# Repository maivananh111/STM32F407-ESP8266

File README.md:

# STM32F407-ESP8266

STM32F407VGT6 and ESP8266 board

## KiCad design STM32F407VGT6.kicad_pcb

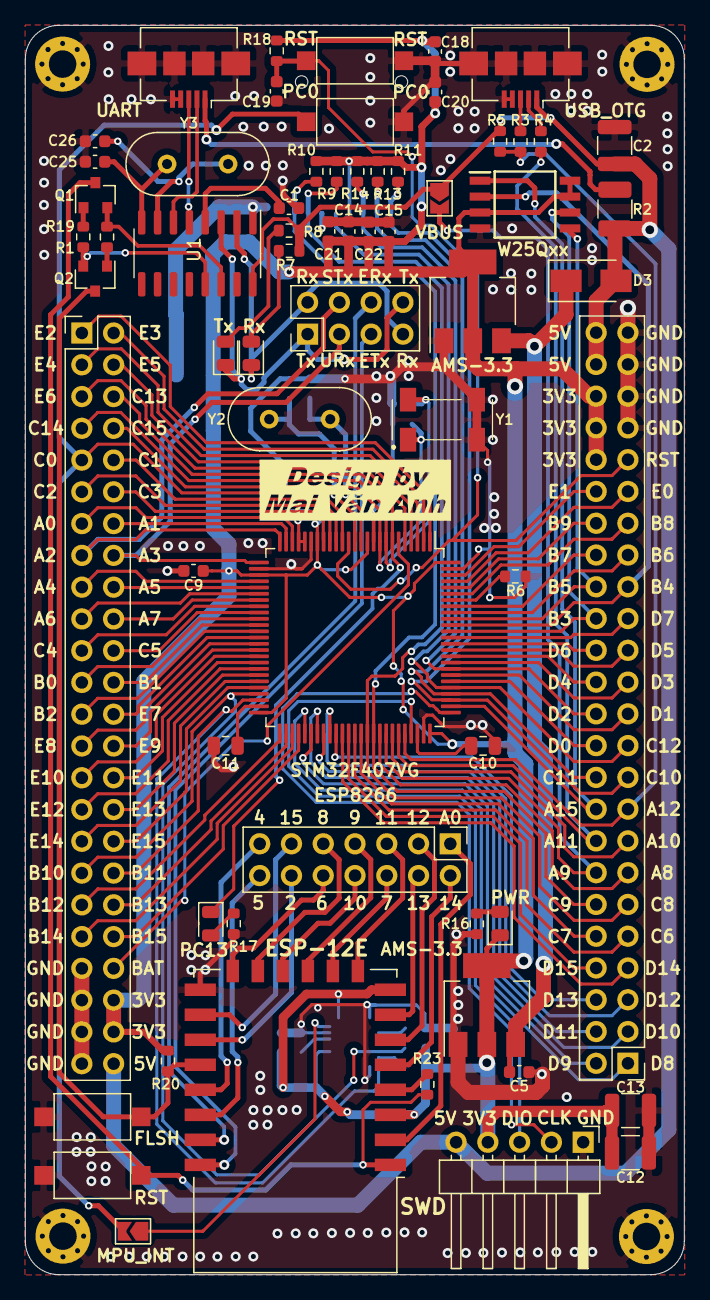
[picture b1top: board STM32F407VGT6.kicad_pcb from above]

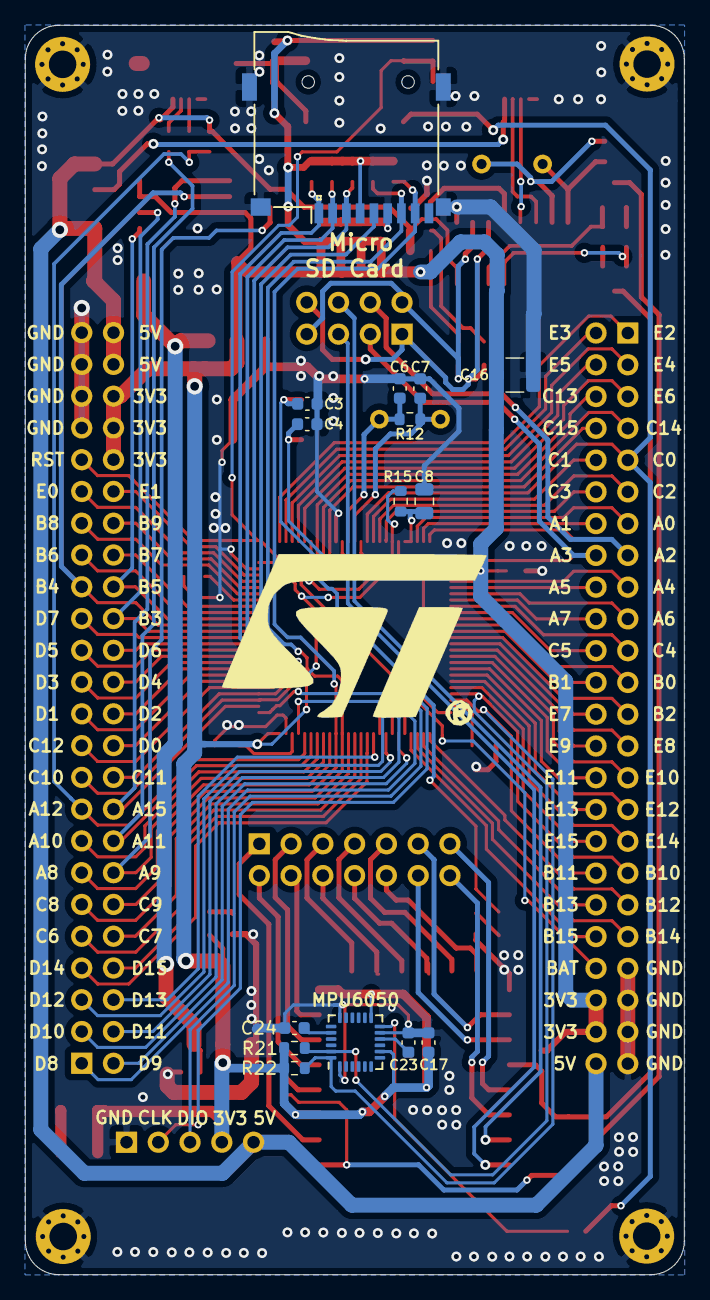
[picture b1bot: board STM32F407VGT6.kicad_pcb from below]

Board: 2 copper layers, 52.7 x 99.9 mm, 85 parts (15 on the bottom side), 132 nets.

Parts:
 : Design
 #2: 1; MountingHole_2.2mm_M2_Pad_Via
 #3: 2; MountingHole_2.2mm_M2_Pad_Via
 #4: 3; MountingHole_2.2mm_M2_Pad_Via
 #5: 4; MountingHole_2.2mm_M2_Pad_Via
 #6: UART_SELECT; PinHeader_2x04_P2.54mm_Vertical
 #7: A; PinHeader_2x24_P2.54mm_Vertical
 #8: B; PinHeader_2x24_P2.54mm_Vertical
AMS-3.3, AMS-3.3#2: AMS1117-3.3; SOT-223-3_TabPin2
C1, C5, C9, C14, C15, C17, C18, C19, C20, C21, C22, C23: 100nF; C_0603_1608Metric
C2, C12, C13, C16: 100uF; C_1210_3225Metric
C3, C4, C6, C7, C25, C26: 22pF; C_0603_1608Metric
C8, C10, C11: 1uF; C_0805_2012Metric
C24: 2.2nF; C_0603_1608Metric
D3: US2AA; D_SMA
ESP8266: ESP_IO; PinHeader_2x07_P2.54mm_Vertical
ESP-12E: ESP-12E
FLSH: ESP_FLS; SW_SPST_CK_RS282G05A3
MPU6050: MPU-6050; InvenSense_QFN-24_4x4mm_P0.5mm
MPU_INT: MPU_INT; SolderJumper-2_P1.3mm_Open_TrianglePad1.0x1.5mm
PC0: USE_BTN; SW_SPST_CK_RS282G05A3
PC13: LED; LED_0805_2012Metric
PWR: LED; LED_0805_2012Metric
Q1, Q2: BC847; SOT-23
R1, R3, R4, R5, R9, R10, R11, R13, R14, R18, R19: 15K; R_0603_1608Metric
R2: 0.1; R_1210_3225Metric_Pad1.30x2.65mm_HandSolder
R6, R20: 10K; R_0603_1608Metric
R7, R8: 1K; R_0603_1608Metric
R12: 100M; R_0603_1608Metric
R15: 47; R_0603_1608Metric
R16, R17: 220; R_0603_1608Metric
R21, R22: 4K7; R_0603_1608Metric
R23: 470; R_0603_1608Metric
RST: ESP_RST; SW_SPST_CK_RS282G05A3
RST#2: RESET; SW_SPST_CK_RS282G05A3
Rx: LED; LED_0805_2012Metric
STM32F407VG: STM32F407VGTx; LQFP-100_14x14mm_P0.5mm
SWD: SWD Programmer; PinHeader_1x05_P2.54mm_Horizontal
Tx: LED; LED_0805_2012Metric
U1: CH340G; SOIC-16_3.9x9.9mm_P1.27mm
UART: USB_B_Micro; USB_Micro-B_Amphenol_10104110_Horizontal
USB_OTG: USB_B_Micro; USB_Micro-B_Amphenol_10104110_Horizontal
VBUS: VBUS; SolderJumper-2_P1.3mm_Open_TrianglePad1.0x1.5mm
W25Qxx: W25Q128JWSIQ; SOIC127P790X216-8N
XS1: SD_Card; Conn_uSDcard
Y1: 32.768KHz; MC306327680KE3ROHS
Y2: 25MHz; Crystal_HC49-4H_Vertical
Y3: 12MHz; Crystal_HC49-4H_Vertical

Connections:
+3V3: #7.44, #7.46, #8.40, #8.42, #8.44, AMS-3.3.2, AMS-3.3#2.2, C9.1, C12.1, C13.1, C14.1, C15.1, C16.1, C17.1, C18.1, C20.1, C21.1, C22.1, ESP-12E.3, ESP-12E.8, MPU6050.8, MPU6050.13, PWR.1, R9.2, R10.2, R11.2, R13.2, R14.2, R15.1, R18.2, R20.2, R21.1, R22.1, STM32F407VG.11, STM32F407VG.19, STM32F407VG.28, STM32F407VG.50, STM32F407VG.75, STM32F407VG.100, SWD.4, W25Qxx.3, W25Qxx.7, W25Qxx.8, XS1.4
+5V: #7.48, #8.46, #8.48, C2.1, D3.2, R2.1, R5.2, R7.2, R8.2, SWD.5, U1.16, USB_OTG.1, VBUS.1
ADC: ESP8266.1, ESP-12E.2
CHE1: C25.2, U1.8, Y3.2
CHE2: C26.2, U1.7, Y3.1
ESP_RST: ESP-12E.1, Q1.3, R23.2, RST.2
ESP_Rx: #6.6, ESP-12E.21
ESP_Tx: #6.5, ESP-12E.22
GND: #2.1, #3.1, #4.1, #5.1, #7.41, #7.43, #7.45, #7.47, #8.41, #8.43, #8.45, #8.47, AMS-3.3.1, AMS-3.3#2.1, C1.2, C2.2, C3.1, C4.1, C5.2, C6.1, C7.1, C8.2, C9.2, C10.1, C11.1, C12.2, C13.2, C14.2, C15.2, C16.2, C17.2, C18.2, C19.2, C20.2, C21.2, C22.2, C23.1, C24.1, C25.1, C26.1, ESP-12E.15, FLSH.1, MPU6050.1, MPU6050.11, MPU6050.18, PC0.1, R6.1, R16.2, R17.2, RST.1, RST#2.1, STM32F407VG.10, STM32F407VG.20, STM32F407VG.27, STM32F407VG.74, STM32F407VG.99, SWD.1, U1.1, UART.4, UART.5, UART.6, USB_OTG.4, USB_OTG.5, USB_OTG.6, W25Qxx.4, XS1.6, Y1.2, Y1.3
GPIO0: ESP-12E.18, FLSH.2, Q2.3, R20.1
HSE1: C6.2, R12.2, STM32F407VG.12, Y2.2
HSE2: C7.2, R12.1, STM32F407VG.13, Y2.1
IO2: ESP8266.12, ESP-12E.17
IO4: ESP8266.13, ESP-12E.19
IO5: ESP8266.14, ESP-12E.20
IO6: ESP8266.10, ESP-12E.14
IO7: ESP8266.6, ESP-12E.10
IO8: ESP8266.9, ESP-12E.13
IO9: ESP8266.7, ESP-12E.11
IO10: ESP8266.8, ESP-12E.12
IO11: ESP8266.5, ESP-12E.9
IO12: ESP8266.3, ESP-12E.6
IO13: ESP8266.4, ESP-12E.7
IO14: ESP8266.2, ESP-12E.5
IO15: ESP8266.11, ESP-12E.16
NRST: #8.39, C19.1, R18.1, RST#2.2, STM32F407VG.14
unnamed: C1.1, U1.4
unnamed: C23.2, MPU6050.10
unnamed: C24.2, MPU6050.20
unnamed: R7.1, Rx.2
unnamed: R8.1, Tx.2
unnamed: PWR.2, R16.1
unnamed: PC13.2, R17.1
unnamed: R2.2, UART.1
unnamed: U1.6, UART.2
unnamed: U1.5, UART.3
unnamed: R4.1, USB_OTG.2
unnamed: R3.1, USB_OTG.3
unnamed: MPU6050.12, MPU_INT.1
unnamed: Q1.1, R1.1
unnamed: Q1.2, R19.1, U1.14
unnamed: Q2.1, R19.2
unnamed: Q2.2, R1.2, U1.13
unnamed: R6.2, STM32F407VG.94
unnamed: ESP-12E.4, R23.1
PA0: #7.13, STM32F407VG.23
PA1: #7.14, STM32F407VG.24
PA2-USART2_TX: #6.4, #7.15, STM32F407VG.25
PA3-USART2_RX: #6.3, #7.16, STM32F407VG.26
PA4: #7.17, STM32F407VG.29
PA5: #7.18, STM32F407VG.30
PA6: #7.19, STM32F407VG.31
PA7: #7.20, STM32F407VG.32
PA8: #8.13, STM32F407VG.67
PA9: #8.14, STM32F407VG.68, VBUS.2
PA10: #8.15, STM32F407VG.69
PA11-USB_DM: #8.16, R4.2, STM32F407VG.70
PA12-USB_DP: #8.17, R3.2, R5.1, STM32F407VG.71
PA15-Flash_CS: #8.18, STM32F407VG.77, W25Qxx.1
PB0: #7.23, STM32F407VG.35
PB1: #7.24, STM32F407VG.36
PB2: #7.25, STM32F407VG.37
PB3-Flash_SCK: #8.30, STM32F407VG.89, W25Qxx.6
PB4-Flash_DO: #8.31, STM32F407VG.90, W25Qxx.2
PB5-Flash_DI: #8.32, STM32F407VG.91, W25Qxx.5
PB6: #8.33, STM32F407VG.92
PB7: #8.34, STM32F407VG.93
PB8: #8.35, STM32F407VG.95
PB9: #8.36, STM32F407VG.96
PB10-MPU_SCL: #7.35, MPU6050.23, R21.2, STM32F407VG.47
PB11-MPU_SDA: #7.36, MPU6050.24, R22.2, STM32F407VG.48
PB12: #7.37, STM32F407VG.51
PB13: #7.38, STM32F407VG.52
PB14: #7.39, STM32F407VG.53
PB15: #7.40, STM32F407VG.54
PC0: #7.9, MPU_INT.2, PC0.2, STM32F407VG.15
PC1: #7.10, STM32F407VG.16
PC2: #7.11, STM32F407VG.17
PC3: #7.12, STM32F407VG.18
PC4: #7.21, STM32F407VG.33
PC5: #7.22, STM32F407VG.34
PC6: #8.9, STM32F407VG.63
PC7: #8.10, STM32F407VG.64
PC8-SDIO_D0: #8.11, R9.1, STM32F407VG.65, XS1.7
PC9-SDIO_D1: #8.12, R10.1, STM32F407VG.66, XS1.8
PC10-SDIO_D2: #8.19, R11.1, STM32F407VG.78, XS1.1
PC11-SDIO_D3: #8.20, R13.1, STM32F407VG.79, XS1.2
PC12-SDIO_CK: #8.21, STM32F407VG.80, XS1.5
PC13: #7.6, PC13.1, STM32F407VG.7
PD0: #8.22, STM32F407VG.81
PD1: #8.23, STM32F407VG.82
PD2-SDIO_CMD: #8.24, R14.1, STM32F407VG.83, XS1.3
PD3: #8.25, STM32F407VG.84
PD4: #8.26, STM32F407VG.85
PD5: #8.27, STM32F407VG.86
PD6: #8.28, STM32F407VG.87
PD7: #8.29, STM32F407VG.88
PD8: #8.1, STM32F407VG.55
PD9: #8.2, STM32F407VG.56
PD10: #8.3, STM32F407VG.57
PD11: #8.4, STM32F407VG.58
PD12: #8.5, STM32F407VG.59
PD13: #8.6, STM32F407VG.60
PD14: #8.7, STM32F407VG.61
PD15: #8.8, STM32F407VG.62
PE0: #8.37, STM32F407VG.97
PE1: #8.38, STM32F407VG.98
PE2: #7.1, STM32F407VG.1
PE3: #7.2, STM32F407VG.2
PE4: #7.3, STM32F407VG.3
PE5: #7.4, STM32F407VG.4
PE6: #7.5, STM32F407VG.5
PE7: #7.26, STM32F407VG.38
PE8: #7.27, STM32F407VG.39
PE9: #7.28, STM32F407VG.40
PE10: #7.29, STM32F407VG.41
PE11: #7.30, STM32F407VG.42
PE12: #7.31, STM32F407VG.43
PE13: #7.32, STM32F407VG.44
PE14: #7.33, STM32F407VG.45
PE15: #7.34, STM32F407VG.46
RTC1: #7.7, C3.2, STM32F407VG.8, Y1.4
RTC2: #7.8, C4.2, STM32F407VG.9, Y1.1
SWCLK: STM32F407VG.76, SWD.2
SWDIO: STM32F407VG.72, SWD.3
USB_Rx: #6.2, #6.7, Rx.1, U1.2
USB_Tx: #6.1, #6.8, Tx.1, U1.3
VBAT: #7.42, STM32F407VG.6
VCAP1: C10.2, STM32F407VG.73
VCAP2: C11.2, STM32F407VG.49
VRef: C8.1, R15.2, STM32F407VG.21, STM32F407VG.22
Vin: AMS-3.3.3, AMS-3.3#2.3, C5.1, D3.1
